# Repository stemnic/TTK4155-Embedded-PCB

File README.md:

# TTK4155-Embedded-PCB
TTK4155 Embedded and Industrial Computer Systems Design - Circuit board

This is the KiCad source files we used for our schematics during the presentation of the project handin and making a physical more robust board for node 1.

## Before

## After

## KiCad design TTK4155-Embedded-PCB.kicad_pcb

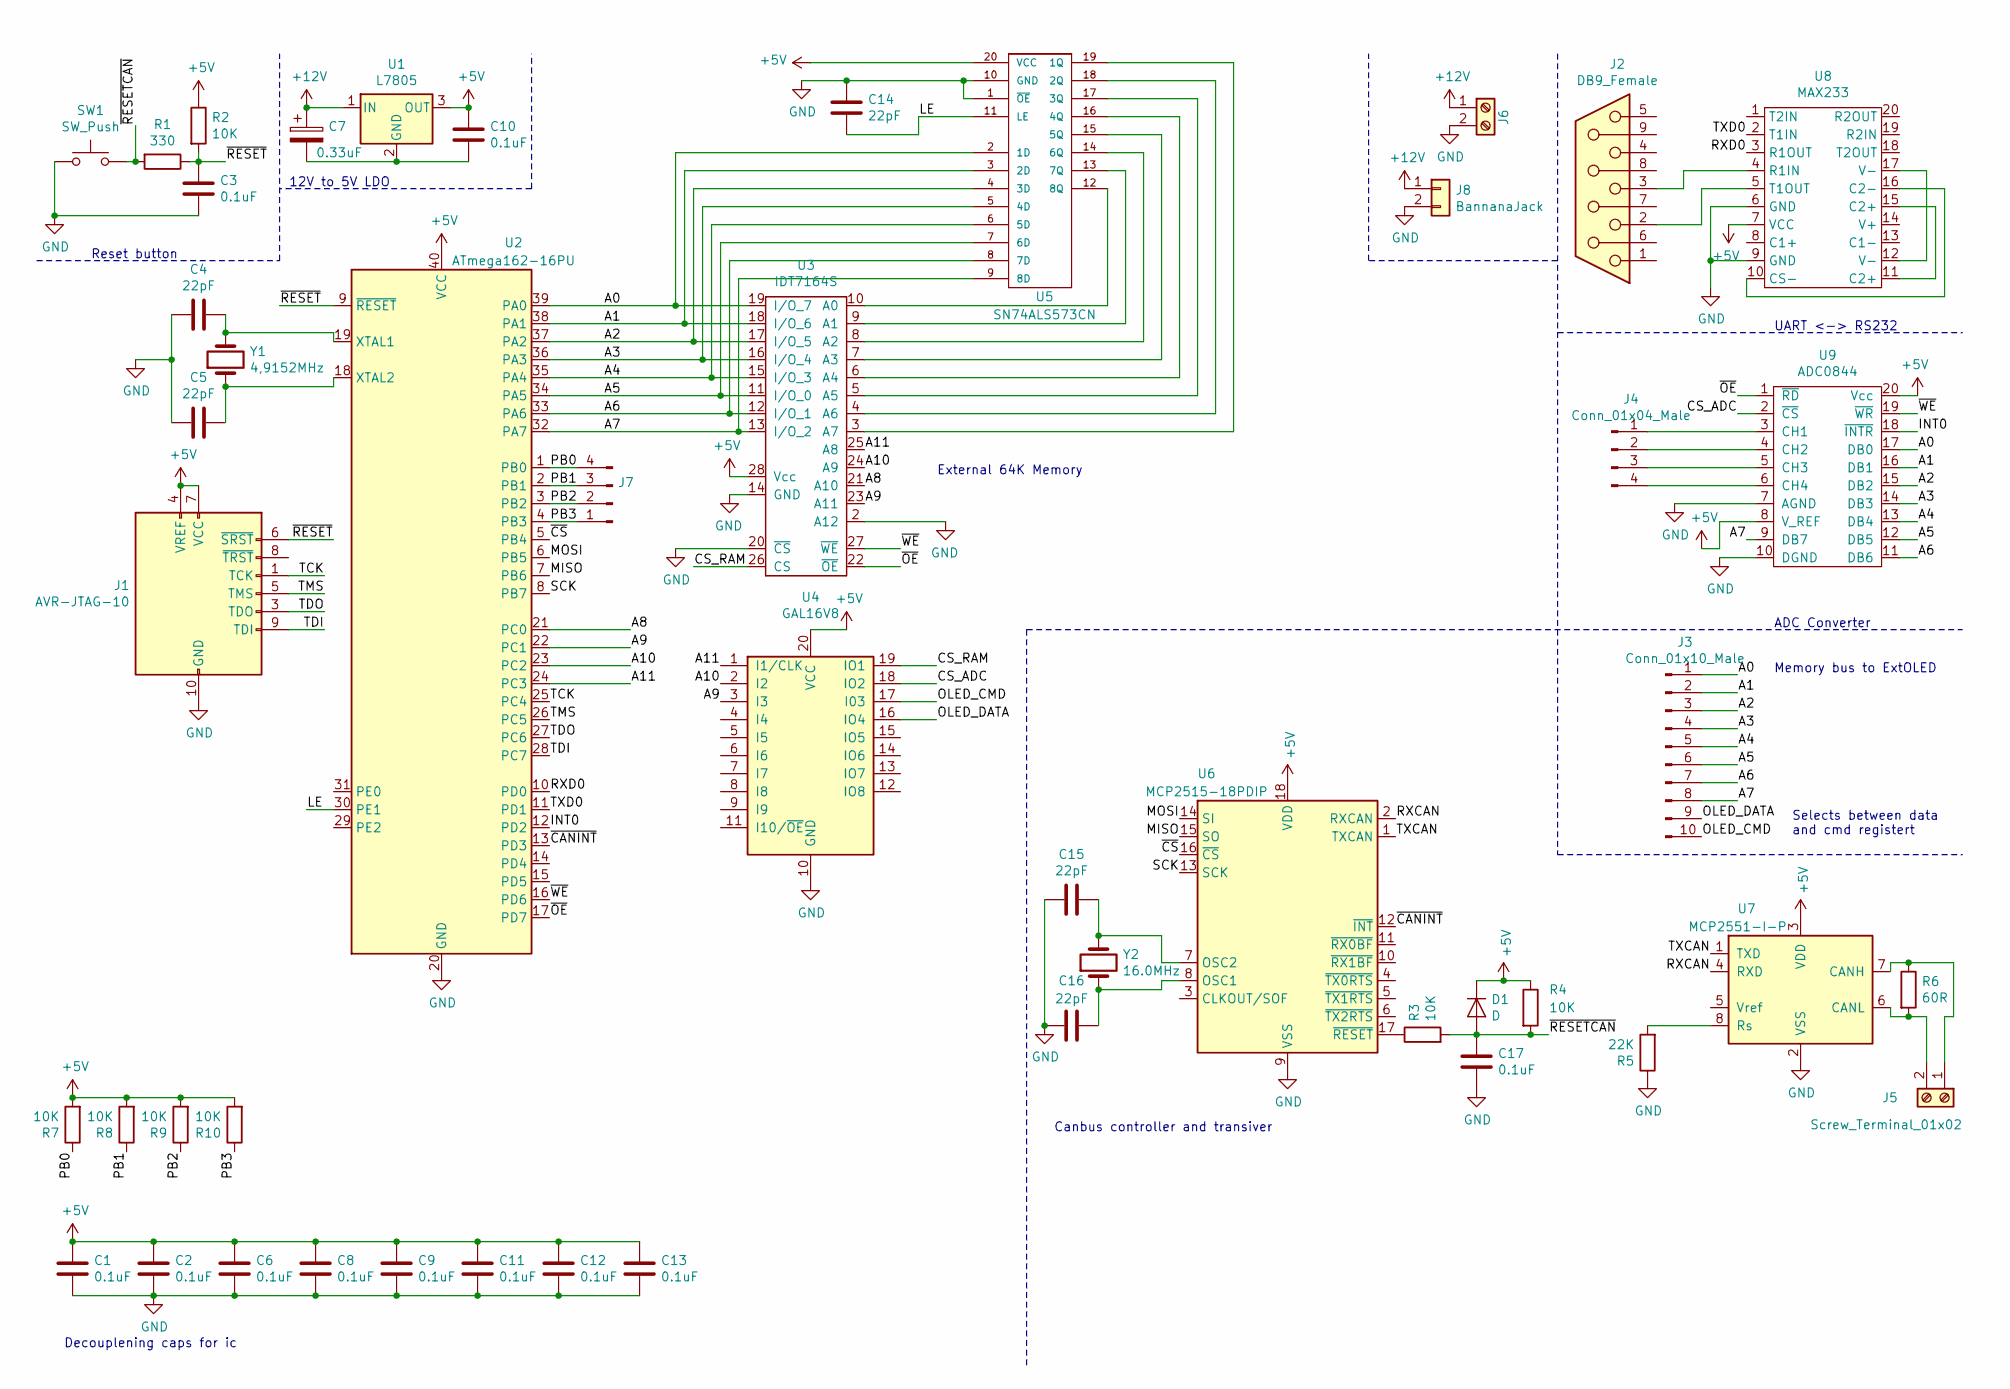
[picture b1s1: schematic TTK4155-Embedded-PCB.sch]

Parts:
C1, C2, C3, C6, C8, C9, C10, C11, C12, C13, C17: 0.1uF; C_0805_2012Metric_Pad1.15x1.40mm_HandSolder
C4, C5, C14, C15, C16: 22pF; C_0805_2012Metric_Pad1.15x1.40mm_HandSolder
C7: 0.33uF; C_Radial_D6.3mm_H7.0mm_P2.50mm
D1: D; D_0805_2012Metric_Pad1.15x1.40mm_HandSolder
J1: AVR-JTAG-10; IDC-Header_2x05_P2.54mm_Vertical
J2: DB9_Female; DSUB-9_Female_Horizontal_P2.77x2.54mm_EdgePinOffset9.40mm
J3: Conn_01x10_Male; PinHeader_1x10_P2.54mm_Vertical
J4, J7: Conn_01x04_Male; PinHeader_1x04_P2.54mm_Vertical
J5, J6: Screw_Terminal_01x02; TerminalBlock_MetzConnect_Type073_RT02602HBLU_1x02_P5.08mm_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
J8: BannanaJack; Banana_Jack_2Pin_15mm_spacing
R1: 330; R_0805_2012Metric_Pad1.15x1.40mm_HandSolder
R2, R3, R4, R7, R8, R9, R10: 10K; R_0805_2012Metric_Pad1.15x1.40mm_HandSolder
R5: 22K; R_0805_2012Metric_Pad1.15x1.40mm_HandSolder
R6: 60R; R_0805_2012Metric_Pad1.15x1.40mm_HandSolder
SW1: SW_Push; SW_PUSH_6mm
U1: L7805; TO-220-3_Horizontal_TabDown
U2: ATmega162-16PU; DIP-40_W15.24mm_Socket
U3: IDT7164S; DIP-28_W7.62mm_Socket_LongPads
U4: GAL16V8; DIP-20_W7.62mm_Socket_LongPads
U5: SN74ALS573CN; DIP-20_W7.62mm_Socket_LongPads
U6: MCP2515-18PDIP; DIP-18_W7.62mm_Socket_LongPads
U7: MCP2551-I-P; DIP-8_W7.62mm_Socket_LongPads
U8: MAX233; DIP-20_W7.62mm_Socket_LongPads
U9: ADC0844; DIP-20_W7.62mm_Socket_LongPads
Y1: 4,9152MHz; Crystal_HC50_Vertical
Y2: 16.0MHz; Crystal_HC50_Vertical

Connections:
+5V: C1.1, C2.1, C6.1, C8.1, C9.1, C10.1, C11.1, C12.1, C13.1, D1.1 (K), J1.4 (VREF), J1.7 (VCC), R2.1, R4.1, R7.2, R8.2, R9.2, R10.2, U1.3 (OUT), U2.40 (VCC), U3.28 (Vcc), U4.20 (VCC), U5.20 (VCC), U6.18 (VDD), U7.3 (VDD), U8.7 (VCC), U9.8 (V_REF), U9.20 (Vcc)
+12V: C7.1, J6.1, J8.1, U1.1 (IN)
/A0: J3.1, U2.39 (PA0), U3.19 (I/O_7), U5.2 (1D), U9.17 (DB0)
/A1: J3.2, U2.38 (PA1), U3.18 (I/O_6), U5.3 (2D), U9.16 (DB1)
/A2: J3.3, U2.37 (PA2), U3.17 (I/O_5), U5.4 (3D), U9.15 (DB2)
/A3: J3.4, U2.36 (PA3), U3.16 (I/O_4), U5.5 (4D), U9.14 (DB3)
/A4: J3.5, U2.35 (PA4), U3.15 (I/O_3), U5.6 (5D), U9.13 (DB4)
/A5: J3.6, U2.34 (PA5), U3.11 (I/O_0), U5.7 (6D), U9.12 (DB5)
/A6: J3.7, U2.33 (PA6), U3.12 (I/O_1), U5.8 (7D), U9.11 (DB6)
/A7: J3.8, U2.32 (PA7), U3.13 (I/O_2), U5.9 (8D), U9.9 (DB7)
/A8: U2.21 (PC0), U3.21 (A10)
/A9: U2.22 (PC1), U3.23 (A11), U4.3 (I3)
/A10: U2.23 (PC2), U3.24 (A9), U4.2 (I2)
/A11: U2.24 (PC3), U3.25 (A8), U4.1 (I1/CLK)
/CS_ADC: U4.18 (IO2), U9.2 (~CS)
/CS_RAM: U3.26 (CS), U4.19 (IO1)
/INT0: U2.12 (PD2), U9.18 (~INTR)
/LE: C14.2, U2.30 (PE1), U5.11 (LE)
/MISO: U2.7 (PB6), U6.15 (SO)
/MOSI: U2.6 (PB5), U6.14 (SI)
/OLED_CMD: J3.10, U4.17 (I03)
/OLED_DATA: J3.9, U4.16 (IO4)
/PB0: J7.4, R7.1, U2.1 (PB0)
/PB1: J7.3, R8.1, U2.2 (PB1)
/PB2: J7.2, R9.1, U2.3 (PB2)
/PB3: J7.1, R10.1, U2.4 (PB3)
/RXCAN: U6.2 (RXCAN), U7.4 (RXD)
/RXD0: U2.10 (PD0), U8.3 (R1OUT)
/SCK: U2.8 (PB7), U6.13 (SCK)
/TCK: J1.1 (TCK), U2.25 (PC4)
/TDI: J1.9 (TDI), U2.28 (PC7)
/TDO: J1.3 (TDO), U2.27 (PC6)
/TMS: J1.5 (TMS), U2.26 (PC5)
/TXCAN: U6.1 (TXCAN), U7.1 (TXD)
/TXD0: U2.11 (PD1), U8.2 (T1IN)
/~CANINT: U2.13 (PD3), U6.12 (~INT)
/~CS: U2.5 (PB4), U6.16 (~CS)
/~OE: U2.17 (PD7), U3.22 (~OE), U9.1 (~RD)
/~RESET: C3.1, J1.6 (~SRST), R1.1, R2.2, U2.9 (~RESET)
/~RESETCAN: C17.1, D1.2 (A), R1.2, R3.2, R4.2, SW1.2
/~WE: U2.16 (PD6), U3.27 (~WE), U9.19 (~WR)
GND: C1.2, C2.2, C3.2, C4.2, C5.1, C6.2, C8.2, C9.2, C11.2, C12.2, C13.2, C14.1, C15.2, C16.1, C17.2, J1.2 (GND), J1.10 (GND), J6.2, J8.2, R5.1, SW1.1, U2.20 (GND), U3.2 (A12), U3.14 (GND), U3.20 (~CS), U4.10 (GND), U5.1 (~OE), U5.10 (GND), U6.9 (VSS), U7.2 (VSS), U8.6 (GND), U8.9 (GND), U9.7 (AGND), U9.10 (DGND)
unnamed: C4.1, U2.19 (XTAL1), Y1.2
unnamed: C5.2, U2.18 (XTAL2), Y1.1
unnamed: C7.2, C10.2, U1.2 (GND)
unnamed: C15.1, U6.7 (OSC2), Y2.2
unnamed: C16.2, U6.8 (OSC1), Y2.1
unnamed: J2.2, U8.5 (T1OUT)
unnamed: J2.3, U8.4 (R1IN)
unnamed: J4.1, U9.3 (CH1)
unnamed: J4.2, U9.4 (CH2)
unnamed: J4.3, U9.5 (CH3)
unnamed: J4.4, U9.6 (CH4)
unnamed: J5.1, R6.1, U7.7 (CANH)
unnamed: J5.2, R6.2, U7.6 (CANL)
unnamed: R3.1, U6.17 (~RESET)
unnamed: R5.2, U7.8 (Rs)
unnamed: U3.3 (A7), U5.19 (1Q)
unnamed: U3.4 (A6), U5.18 (2Q)
unnamed: U3.5 (A5), U5.17 (3Q)
unnamed: U3.6 (A4), U5.16 (4Q)
unnamed: U3.7 (A3), U5.15 (5Q)
unnamed: U3.8 (A2), U5.14 (6Q)
unnamed: U3.9 (A1), U5.13 (7Q)
unnamed: U3.10 (A0), U5.12 (8Q)
unnamed: U8.10 (CS-), U8.16 (C2-)
unnamed: U8.11 (C2+), U8.15 (C2+)
unnamed: U8.12 (V-), U8.17 (V-)

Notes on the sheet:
Decouplening caps for ic
UART <-> RS232
External 64K Memory
Reset button
12V to 5V LDO
ADC Converter
Memory bus to ExtOLED
Selects between data and cmd registert
Canbus controller and transiver

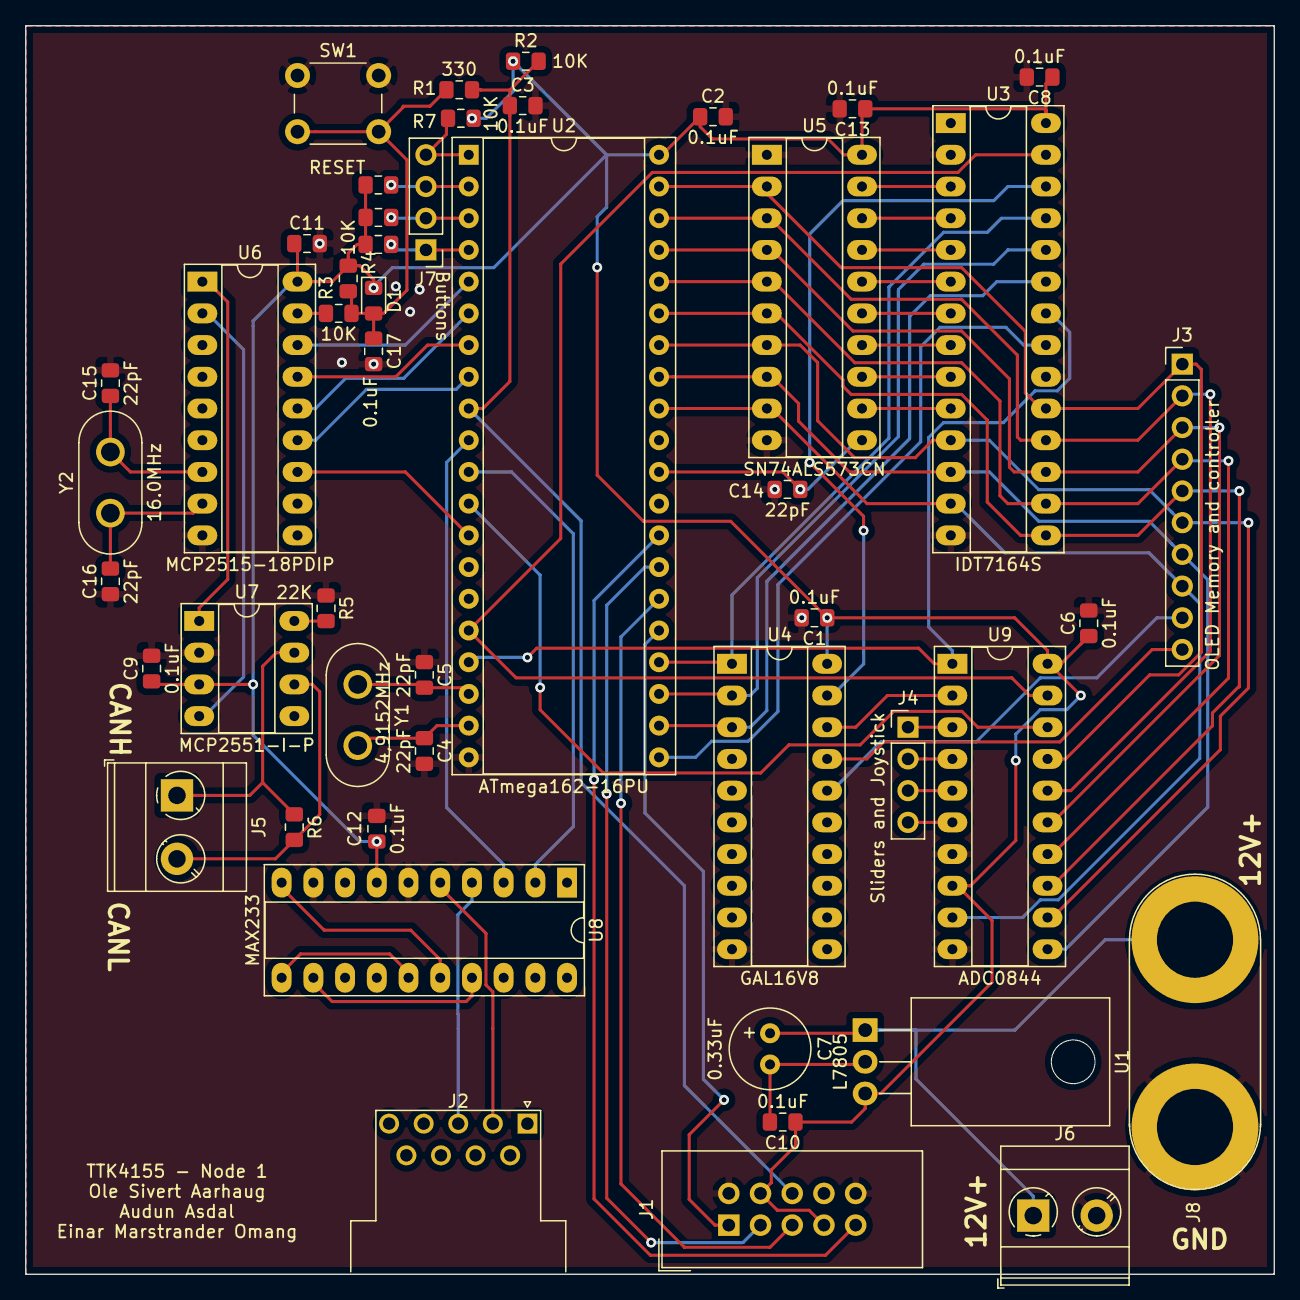
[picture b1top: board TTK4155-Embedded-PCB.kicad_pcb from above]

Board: 2 copper layers, 100.0 x 100.0 mm, 48 parts (0 on the bottom side), 68 nets.

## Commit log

2019-10-25 stated working on pcb
2019-10-25 Started tracing
2019-10-25 Finished first revision of board
2019-10-25 Fixed missing pullup
2019-10-25 Made som esmall changes and send pcb to production
2019-11-15 Fixed schematics to reflects bodges in rev 1
2019-11-15 Changed folder structure
2019-11-15 added node2
2019-11-15 small fixes in node2
2019-11-15 Resctructure folders
2019-11-15 added gitignore
2019-11-15 Another restructure
2019-11-15 deleted file in gitignore
2019-11-15 removed all gitignore files
2020-05-25 Uploaded before and after jpegs
